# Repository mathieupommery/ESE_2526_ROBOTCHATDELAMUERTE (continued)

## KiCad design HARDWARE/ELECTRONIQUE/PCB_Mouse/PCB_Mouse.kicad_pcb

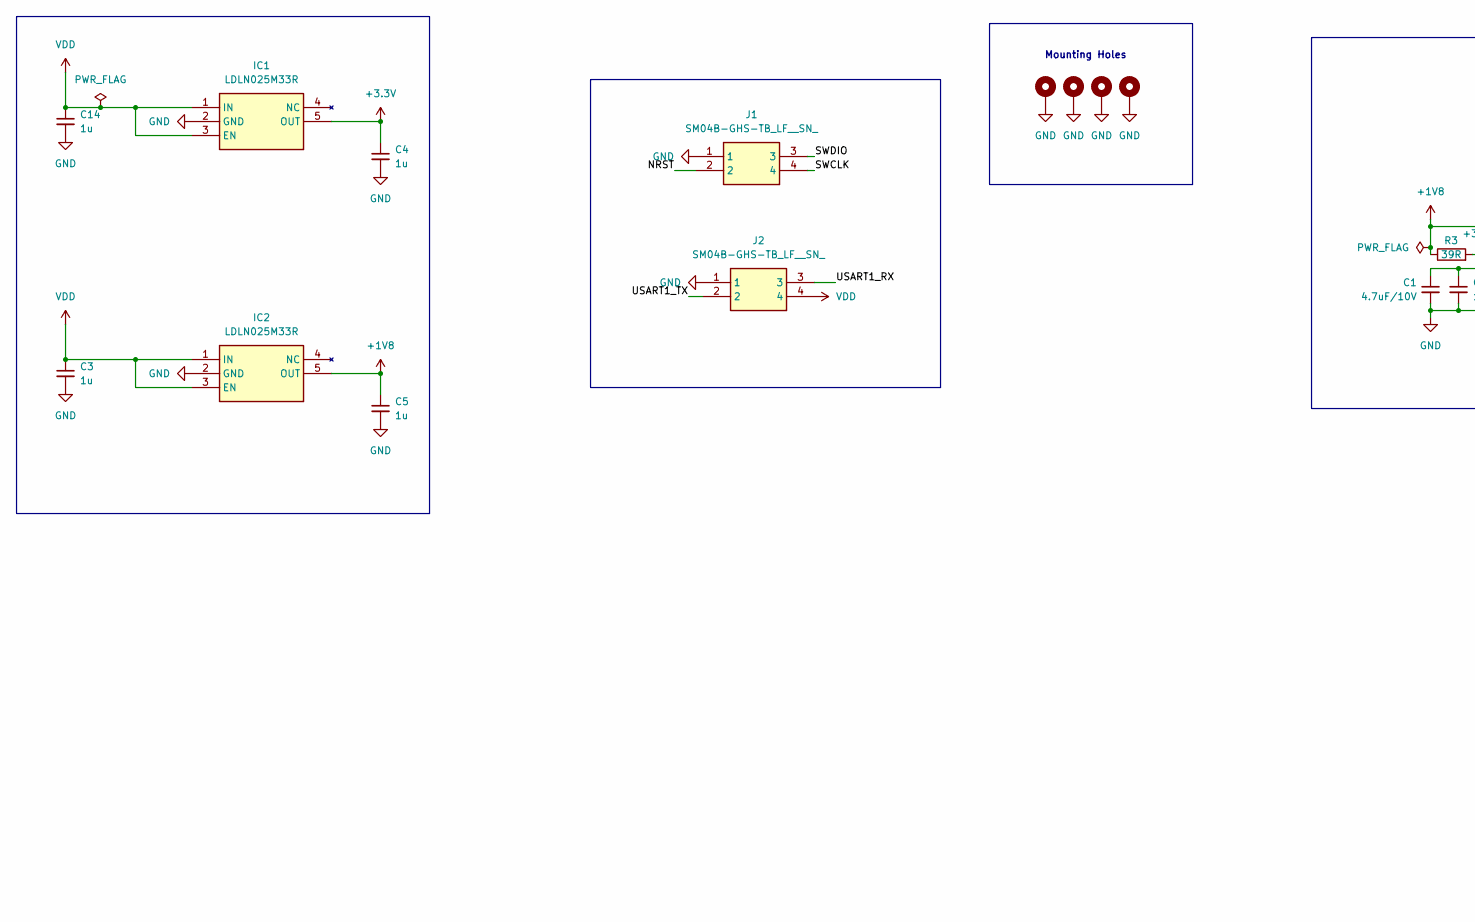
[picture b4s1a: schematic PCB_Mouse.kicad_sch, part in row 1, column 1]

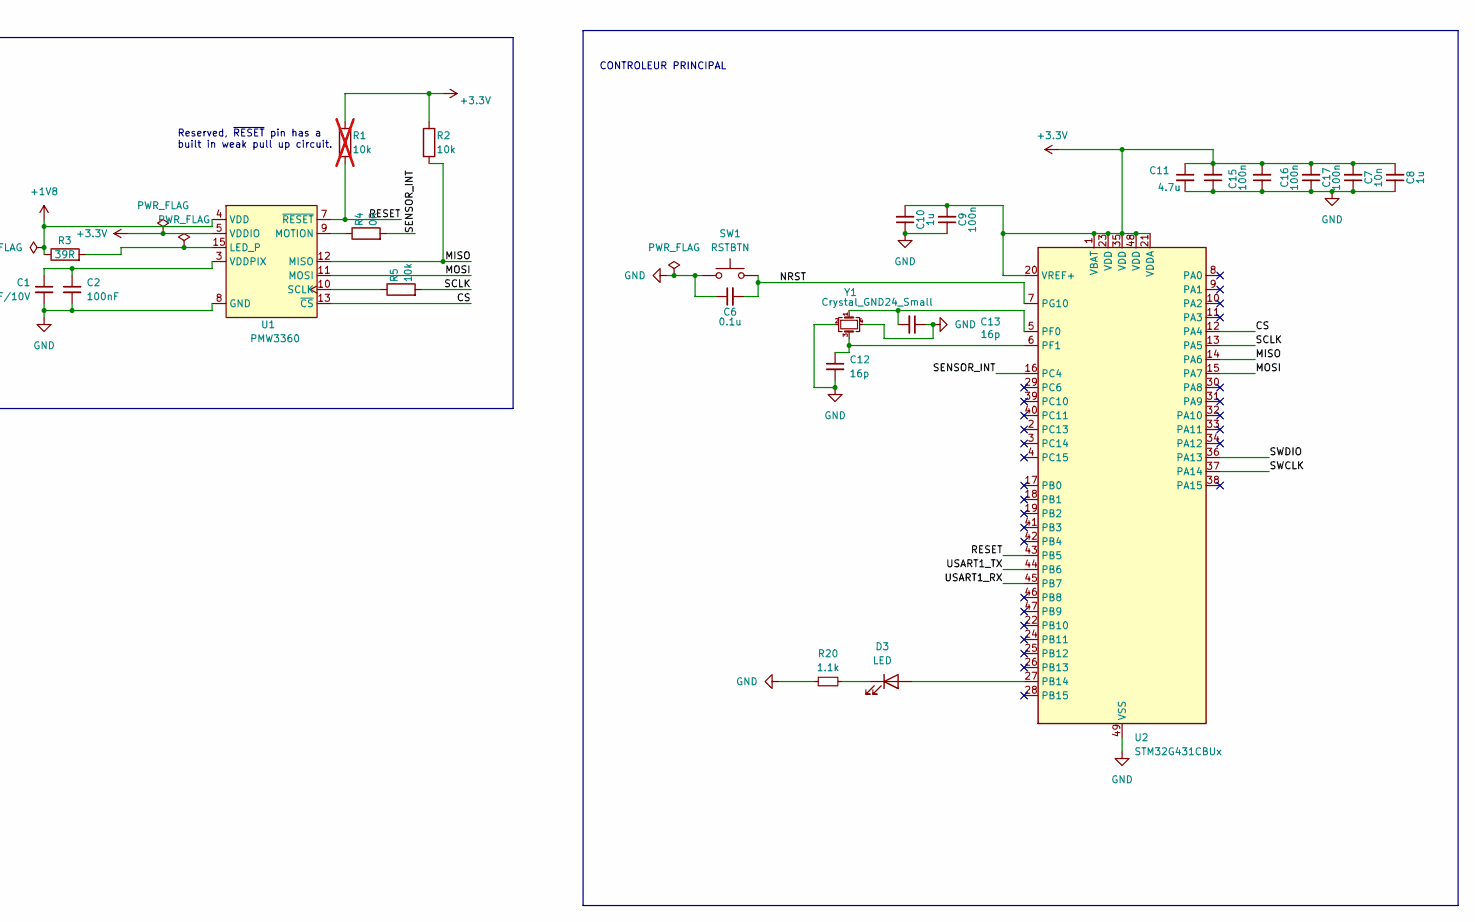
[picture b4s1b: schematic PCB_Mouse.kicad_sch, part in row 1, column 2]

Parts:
C1: 4.7uF/10V; C_0603_1608Metric_Pad1.08x0.95mm_HandSolder
C2: 100nF; C_0402_1005Metric
C3, C4, C5, C8, C10, C14: 1u; C_0402_1005Metric
C6: 0.1u; C_0402_1005Metric
C7: 10n; C_0402_1005Metric
C9, C15, C16, C17: 100n; C_0402_1005Metric
C11: 4.7u; C_0402_1005Metric
C12, C13: 16p; C_0402_1005Metric
D3: LED; LED_0402_1005Metric
H1, H2, H3, H4: MountingHole_Pad; MountingHole_2.2mm_M2_ISO14580_Pad
IC1, IC2: LDLN025M33R; SOT95P280X145-5N; Manufacturer_Part_Number LDLN025M33R; Mouser Part Number 511-LDLN025M33R
J1, J2: SM04B-GHS-TB_LF__SN_; SM04B-GHS-TB; Manufacturer_Part_Number SM04B-GHS-TB(LF)(SN); Mouser Part Number N/A
R1: 10k; R_0402_1005Metric; not fitted
R2, R5: 10k; R_0402_1005Metric
R3: 39R; R_0402_1005Metric
R4: 0R; R_0402_1005Metric
R20: 1.1k; R_0402_1005Metric
SW1: RSTBTN; KXT341LHS
U1: PMW3360
U2: STM32G431CBUx; QFN-48-1EP_7x7mm_P0.5mm_EP5.6x5.6mm
Y1: Crystal_GND24_Small; LFXTAL069527REEL

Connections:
+1V8: C5.1, IC2.5 (OUT), R3.1, U1.4 (VDD)
+3.3V: C4.1, C7.2, C8.2, C9.2, C10.2, C11.1, C15.2, C16.2, C17.2, IC1.5 (OUT), R1.1, R2.1, U1.5 (VDDIO), U2.1 (VBAT), U2.20 (VREF+), U2.21 (VDDA), U2.23 (VDD), U2.35 (VDD), U2.48 (VDD)
/CS: U1.13 (~CS), U2.12 (PA4)
/MISO: R2.2, U1.12 (MISO), U2.14 (PA6)
/MOSI: U1.11 (MOSI), U2.15 (PA7)
/NRST: C6.2, J1.2, SW1.2, U2.7 (PG10)
/RESET: R1.2, U1.7 (~RESET), U2.43 (PB5)
/SCLK: R5.2, U2.13 (PA5)
/SENSOR_INT: R4.2, U2.16 (PC4)
/SWCLK: J1.4, U2.37 (PA14)
/SWDIO: J1.3, U2.36 (PA13)
/USART1_RX: J2.3, U2.45 (PB7)
/USART1_TX: J2.2, U2.44 (PB6)
GND: C1.2, C2.2, C3.2, C4.2, C5.2, C6.1, C7.1, C8.1, C9.1, C10.1, C11.2, C12.2, C13.1, C14.2, C15.1, C16.1, C17.1, H1.1, H2.1, H3.1, H4.1, IC1.2 (GND), IC2.2 (GND), J1.1, J2.1, R20.1, SW1.1, U1.8 (GND), U2.49 (VSS), Y1.2, Y1.4
unnamed: D3.2 (A), U2.27 (PB14)
unnamed: D3.1 (K), R20.2
unnamed: R3.2, U1.15 (LED_P)
unnamed: R4.1, U1.9 (MOTION)
unnamed: R5.1, U1.10 (SCLK)
unnamed: C1.1, C2.1, U1.3 (VDDPIX)
unnamed: C13.2, U2.5 (PF0), Y1.1
unnamed: C12.1, U2.6 (PF1), Y1.3
VDD: C3.1, C14.1, IC1.1 (IN), IC1.3 (EN), IC2.1 (IN), IC2.3 (EN), J2.4

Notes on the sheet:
Reserved, ~{RESET} pin has a built in weak pull up circuit.
CONTROLEUR PRINCIPAL
Mounting Holes

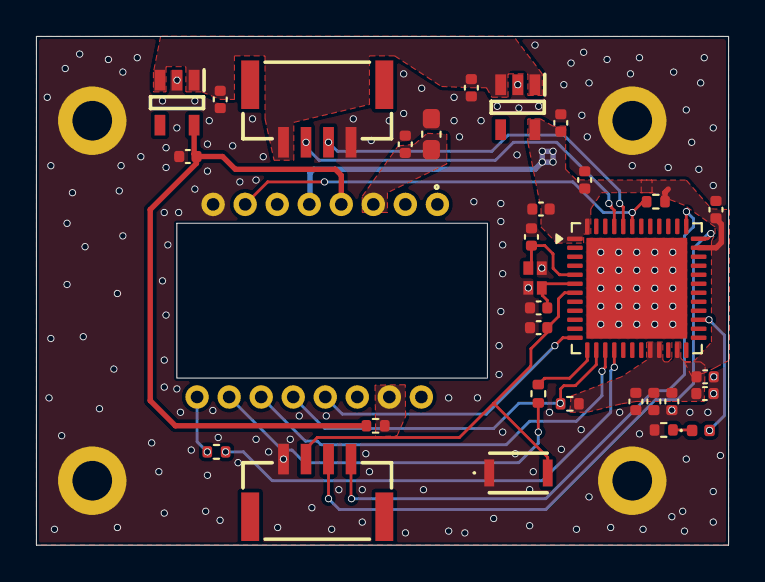
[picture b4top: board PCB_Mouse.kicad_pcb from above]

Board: 2 copper layers, 38.4 x 28.3 mm, 36 parts (0 on the bottom side), 23 nets.

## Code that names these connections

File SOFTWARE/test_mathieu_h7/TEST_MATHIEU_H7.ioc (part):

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Mcu.Name=STM32H743V(G-I)Hx
Mcu.Package=TFBGA100
Mcu.UserName=STM32H743VIHx
PA0.Mode=Asynchronous
PA0.Signal=UART4_TX
PA1.Mode=Asynchronous
PA1.Signal=UART4_RX
PA10.GPIOParameters=GPIO_Label
PA10.GPIO_Label=GPIO_MOT3
PA10.Signal=GPXTI10
PA11.Mode=Device_Only
PA11.Signal=USB_OTG_FS_DM
PA12.Mode=Device_Only
PA12.Signal=USB_OTG_FS_DP
PA13\ (JTMS/SWDIO).Mode=Serial_Wire
PA13\ (JTMS/SWDIO).Signal=DEBUG_JTMS-SWDIO
PA14\ (JTCK/SWCLK).Mode=Serial_Wire
PA14\ (JTCK/SWCLK).Signal=DEBUG_JTCK-SWCLK
PA15\ (JTDI).Signal=SPI1_NSS
PA3.Signal=GPXTI3
PA4.Signal=GPIO_Output
PA8.Mode=I2C
PA8.Signal=I2C3_SCL
PB1.Signal=S_TIM3_CH4
PB10.Mode=I2C
PB10.Signal=I2C2_SCL
PB11.Mode=I2C
PB11.Signal=I2C2_SDA
PB12.Signal=GPXTI12
PB14.Mode=Asynchronous
PB14.Signal=USART1_TX
PB15.Mode=Asynchronous
PB15.Signal=USART1_RX
PB3\ (JTDO/TRACESWO).Mode=Full_Duplex_Master
PB3\ (JTDO/TRACESWO).Signal=SPI1_SCK
PB4\ (NJTRST).Mode=Full_Duplex_Master
PB4\ (NJTRST).Signal=SPI1_MISO
PB5.Mode=Full_Duplex_Master
PB5.Signal=SPI1_MOSI
PB7.Signal=S_TIM4_CH2
PB8.Mode=I2C
PB8.Signal=I2C1_SCL
PB9.Mode=I2C
PB9.Signal=I2C1_SDA
PC0.Signal=GPXTI0
PC1.Signal=GPIO_Output
PC11.Signal=GPXTI11
PC2_C.Signal=GPXTI2
PC6.Mode=Asynchronous
PC6.Signal=USART6_TX
PC7.Mode=Asynchronous
PC7.Signal=USART6_RX
PC9.Mode=I2C
PC9.Signal=I2C3_SDA
PD0.Mode=SAI_A_Master
PD0.Signal=SAI3_SCK_A
PD1.Mode=SAI_A_Master
PD1.Signal=SAI3_SD_A
PD10.GPIOParameters=GPIO_Label
PD10.GPIO_Label=LED1
PD10.Signal=GPIO_Output
PD11.GPIOParameters=GPIO_Label
PD11.GPIO_Label=LED0
PD11.Signal=GPIO_Output
PD12.Mode=I2C
PD12.Signal=I2C4_SCL
PD13.Mode=I2C
PD13.Signal=I2C4_SDA
PD4.Mode=SAI_A_Master
PD4.Signal=SAI3_FS_A
PD8.Mode=Asynchronous
PD8.Signal=USART3_TX
PD9.Mode=Asynchronous
PD9.Signal=USART3_RX
PE0.Mode=Asynchronous
PE0.Signal=UART8_RX
PE1.Mode=Asynchronous
PE1.Signal=UART8_TX
PE15.Signal=GPIO_Output
PE2.Mode=Full_Duplex_Master
PE2.Signal=SPI4_SCK
PE5.Mode=Full_Duplex_Master
PE5.Signal=SPI4_MISO
PE6.Mode=Full_Duplex_Master
PE6.Signal=SPI4_MOSI
PE7.Mode=Asynchronous
PE7.Signal=UART7_RX
PE8.Mode=Asynchronous
PE8.Signal=UART7_TX
PH0-OSC_IN\ (PH0).Mode=HSE-External-Oscillator
PH0-OSC_IN\ (PH0).Signal=RCC_OSC_IN
PH1-OSC_OUT\ (PH1).Mode=HSE-External-Oscillator
PH1-OSC_OUT\ (PH1).Signal=RCC_OSC_OUT
RCC.HSE_VALUE=8000000
RCC.SYSCLKFreq_VALUE=480000000
RCC.SYSCLKSource=RCC_SYSCLKSOURCE_PLLCLK
board=custom

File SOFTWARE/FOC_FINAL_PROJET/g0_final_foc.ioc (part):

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Mcu.Name=STM32G031C(4-6-8)Tx
Mcu.Package=LQFP48
Mcu.UserName=STM32G031C8Tx
PA0.Mode=Full_Duplex_Master
PA0.Signal=SPI2_SCK
PA1.GPIOParameters=GPIO_Label
PA1.GPIO_Label=MGH
PA1.Signal=GPIO_Input
PA10.GPIOParameters=GPIO_Speed,GPIO_PuPd,GPIO_Label
PA10.GPIO_Label=HSW
PA10.GPIO_PuPd=GPIO_PULLDOWN
PA10.GPIO_Speed=GPIO_SPEED_FREQ_HIGH
PA10.Signal=S_TIM1_CH3
PA11\ [PA9].GPIOParameters=PinState,GPIO_PuPd,GPIO_Label
PA11\ [PA9].GPIO_Label=OC_SEL
PA11\ [PA9].GPIO_PuPd=GPIO_PULLDOWN
PA11\ [PA9].PinState=GPIO_PIN_SET
PA11\ [PA9].Signal=GPIO_Output
PA12\ [PA10].GPIOParameters=GPIO_Label
PA12\ [PA10].GPIO_Label=BTN
PA12\ [PA10].Signal=GPXTI12
PA13.Mode=Serial_Wire
PA13.Signal=SYS_SWDIO
PA14-BOOT0.Mode=Serial_Wire
PA14-BOOT0.Signal=SYS_SWCLK
PA15.GPIOParameters=GPIO_Label
PA15.GPIO_Label=HALL_CS
PA15.Signal=GPIO_Output
PA2.Mode=Asynchronous
PA2.Signal=LPUART1_TX
PA3.Mode=Asynchronous
PA3.Signal=LPUART1_RX
PA4.GPIOParameters=GPIO_Label
PA4.GPIO_Label=MGL
PA4.Signal=GPIO_Input
PA5.GPIOParameters=GPIO_Label
PA5.GPIO_Label=VBAT/TEMP
PA5.Mode=IN5
PA5.Signal=ADC1_IN5
PA6.GPIOParameters=GPIO_Label
PA6.GPIO_Label=ISNSV
PA6.Mode=IN6
PA6.Signal=ADC1_IN6
PA7.GPIOParameters=GPIO_Label
PA7.GPIO_Label=ISNSU
PA7.Mode=IN7
PA7.Signal=ADC1_IN7
PA8.GPIOParameters=GPIO_Speed,GPIO_PuPd,GPIO_Label
PA8.GPIO_Label=HSU
PA8.GPIO_PuPd=GPIO_PULLDOWN
PA8.GPIO_Speed=GPIO_SPEED_FREQ_HIGH
PA8.Signal=S_TIM1_CH1
PA9.GPIOParameters=GPIO_Speed,GPIO_PuPd,GPIO_Label
PA9.GPIO_Label=HSV
PA9.GPIO_PuPd=GPIO_PULLDOWN
PA9.GPIO_Speed=GPIO_SPEED_FREQ_HIGH
PA9.Signal=S_TIM1_CH2
PB1.GPIOParameters=GPIO_Label
PB1.GPIO_Label=ISNSW
PB1.Mode=IN9
PB1.Signal=ADC1_IN9
PB12.GPIOParameters=GPIO_PuPd,GPIO_Label
PB12.GPIO_Label=OVERCURRENT
PB12.GPIO_PuPd=GPIO_PULLDOWN
PB12.Mode=Activate-Break-Input
PB12.Signal=TIM1_BK
PB13.GPIOParameters=GPIO_Speed,GPIO_PuPd,GPIO_Label
PB13.GPIO_Label=LSU
PB13.GPIO_PuPd=GPIO_PULLDOWN
PB13.GPIO_Speed=GPIO_SPEED_FREQ_HIGH
PB13.Mode=PWM Generation1 CH1 CH1N
PB13.Signal=TIM1_CH1N
PB14.GPIOParameters=GPIO_Speed,GPIO_PuPd,GPIO_Label
PB14.GPIO_Label=LSV
PB14.GPIO_PuPd=GPIO_PULLDOWN
PB14.GPIO_Speed=GPIO_SPEED_FREQ_HIGH
PB14.Mode=PWM Generation2 CH2 CH2N
PB14.Signal=TIM1_CH2N
PB15.GPIOParameters=GPIO_Speed,GPIO_PuPd,GPIO_Label
PB15.GPIO_Label=LSW
PB15.GPIO_PuPd=GPIO_PULLDOWN
PB15.GPIO_Speed=GPIO_SPEED_FREQ_HIGH
PB15.Mode=PWM Generation3 CH3 CH3N
PB15.Signal=TIM1_CH3N
PB6.Mode=Full_Duplex_Master
PB6.Signal=SPI2_MISO
PB7.Mode=Full_Duplex_Master
PB7.Signal=SPI2_MOSI
PF0-OSC_IN\ (PF0).GPIOParameters=GPIO_Label
PF0-OSC_IN\ (PF0).GPIO_Label=LED
PF0-OSC_IN\ (PF0).Signal=GPIO_Output
RCC.HSE_VALUE=8000000
RCC.SYSCLKFreq_VALUE=64000000
RCC.SYSCLKSource=RCC_SYSCLKSOURCE_PLLCLK
board=custom

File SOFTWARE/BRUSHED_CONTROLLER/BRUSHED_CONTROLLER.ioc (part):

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Mcu.Name=STM32G431C(6-8-B)Ux
Mcu.Package=UFQFPN48
Mcu.UserName=STM32G431CBUx
PA0.Signal=S_TIM2_CH1
PA1.Signal=S_TIM2_CH2
PA11.Signal=S_TIM4_CH1
PA12.Signal=S_TIM4_CH2
PA13.Mode=Serial_Wire
PA13.Signal=SYS_JTMS-SWDIO
PA14.Mode=Serial_Wire
PA14.Signal=SYS_JTCK-SWCLK
PA4.Signal=S_TIM3_CH2
PA8.Signal=S_TIM1_CH1
PA9.Signal=S_TIM1_CH2
PB0.Signal=S_TIM3_CH3
PB1.Signal=S_TIM3_CH4
PB10.Mode=Asynchronous
PB10.Signal=USART3_TX
PB11.Mode=Asynchronous
PB11.Signal=USART3_RX
PB15.Mode=IN15-Single-Ended
PB15.Signal=ADC2_IN15
PB2.Signal=GPXTI2
PB6.Signal=S_TIM8_CH1
PB8-BOOT0.Signal=S_TIM8_CH2
PC10.Signal=GPXTI10
PC13.GPIOParameters=GPIO_Label
PC13.GPIO_Label=LED
PC13.Signal=GPIO_Output
PC4.Signal=ADC2_IN5
PC6.Signal=S_TIM3_CH1
PF0-OSC_IN.Mode=HSE-External-Oscillator
PF0-OSC_IN.Signal=RCC_OSC_IN
PF1-OSC_OUT.Mode=HSE-External-Oscillator
PF1-OSC_OUT.Signal=RCC_OSC_OUT
RCC.HSE_VALUE=24000000
RCC.SYSCLKFreq_VALUE=120000000
RCC.SYSCLKSource=RCC_SYSCLKSOURCE_PLLCLK
board=custom

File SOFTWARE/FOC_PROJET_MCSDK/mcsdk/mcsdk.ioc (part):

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Mcu.Name=STM32G031C(4-6-8)Tx
Mcu.Package=LQFP48
Mcu.UserName=STM32G031C8Tx
PA10.GPIOParameters=GPIO_Speed,GPIO_PuPd,GPIO_Label
PA10.GPIO_Label=M1_PWM_WH
PA10.GPIO_PuPd=GPIO_PULLDOWN
PA10.GPIO_Speed=GPIO_SPEED_FREQ_HIGH
PA10.Signal=S_TIM1_CH3
PA11\ [PA9].GPIOParameters=PinState,GPIO_PuPd,GPIO_Label
PA11\ [PA9].GPIO_Label=OC_SEL
PA11\ [PA9].GPIO_PuPd=GPIO_PULLDOWN
PA11\ [PA9].PinState=GPIO_PIN_SET
PA11\ [PA9].Signal=GPIO_Output
PA13.GPIOParameters=GPIO_Label
PA13.GPIO_Label=TMS
PA13.Mode=Serial_Wire
PA13.Signal=SYS_SWDIO
PA14-BOOT0.GPIOParameters=GPIO_Label
PA14-BOOT0.GPIO_Label=TCK
PA14-BOOT0.Mode=Serial_Wire
PA14-BOOT0.Signal=SYS_SWCLK
PA4.GPIOParameters=GPIO_Label
PA4.GPIO_Label=M1_BUS_VOLTAGE
PA4.Mode=IN4
PA4.Signal=ADC1_IN4
PA5.GPIOParameters=GPIO_Label
PA5.GPIO_Label=M1_TEMPERATURE
PA5.Mode=IN5
PA5.Signal=ADC1_IN5
PA6.GPIOParameters=GPIO_Label
PA6.GPIO_Label=M1_CURR_AMPL_U
PA6.Mode=IN6
PA6.Signal=ADC1_IN6
PA7.GPIOParameters=GPIO_Label
PA7.GPIO_Label=M1_CURR_AMPL_V
PA7.Mode=IN7
PA7.Signal=ADC1_IN7
PA8.GPIOParameters=GPIO_Speed,GPIO_PuPd,GPIO_Label
PA8.GPIO_Label=M1_PWM_UH
PA8.GPIO_PuPd=GPIO_PULLDOWN
PA8.GPIO_Speed=GPIO_SPEED_FREQ_HIGH
PA8.Signal=S_TIM1_CH1
PA9.GPIOParameters=GPIO_Speed,GPIO_PuPd,GPIO_Label
PA9.GPIO_Label=M1_PWM_VH
PA9.GPIO_PuPd=GPIO_PULLDOWN
PA9.GPIO_Speed=GPIO_SPEED_FREQ_HIGH
PA9.Signal=S_TIM1_CH2
PB1.GPIOParameters=GPIO_Label
PB1.GPIO_Label=M1_CURR_AMPL_W
PB1.Mode=IN9
PB1.Signal=ADC1_IN9
PB12.GPIOParameters=GPIO_PuPd,GPIO_Label
PB12.GPIO_Label=M1_OCP
PB12.GPIO_PuPd=GPIO_PULLDOWN
PB12.Mode=Activate-Break-Input
PB12.Signal=TIM1_BK
PB13.GPIOParameters=GPIO_Speed,GPIO_PuPd,GPIO_Label
PB13.GPIO_Label=M1_PWM_UL
PB13.GPIO_PuPd=GPIO_PULLDOWN
PB13.GPIO_Speed=GPIO_SPEED_FREQ_HIGH
PB13.Mode=PWM Generation1 CH1 CH1N
PB13.Signal=TIM1_CH1N
PB14.GPIOParameters=GPIO_Speed,GPIO_PuPd,GPIO_Label
PB14.GPIO_Label=M1_PWM_VL
PB14.GPIO_PuPd=GPIO_PULLDOWN
PB14.GPIO_Speed=GPIO_SPEED_FREQ_HIGH
PB14.Mode=PWM Generation2 CH2 CH2N
PB14.Signal=TIM1_CH2N
PB15.GPIOParameters=GPIO_Speed,GPIO_PuPd,GPIO_Label
PB15.GPIO_Label=M1_PWM_WL
PB15.GPIO_PuPd=GPIO_PULLDOWN
PB15.GPIO_Speed=GPIO_SPEED_FREQ_HIGH
PB15.Mode=PWM Generation3 CH3 CH3N
PB15.Signal=TIM1_CH3N
PB6.GPIOParameters=GPIO_Speed,GPIO_PuPd,GPIO_Label,GPIO_Mode
PB6.GPIO_Label=UART_TX
PB6.GPIO_Mode=GPIO_MODE_AF_PP
PB6.GPIO_PuPd=GPIO_NOPULL
PB6.GPIO_Speed=GPIO_SPEED_FREQ_LOW
PB6.Mode=Asynchronous
PB6.Signal=USART1_TX
PB7.GPIOParameters=GPIO_Speed,GPIO_PuPd,GPIO_Label,GPIO_Mode
PB7.GPIO_Label=UART_RX
PB7.GPIO_Mode=GPIO_MODE_AF_PP
PB7.GPIO_PuPd=GPIO_NOPULL
PB7.GPIO_Speed=GPIO_SPEED_FREQ_LOW
PB7.Mode=Asynchronous
PB7.Signal=USART1_RX
PC14-OSC32_IN\ (PC14).GPIOParameters=GPIO_PuPd,GPIO_Label,GPIO_ModeDefaultEXTI
PC14-OSC32_IN\ (PC14).GPIO_Label=Start/Stop [PushButton]
PC14-OSC32_IN\ (PC14).GPIO_ModeDefaultEXTI=GPIO_MODE_IT_FALLING
PC14-OSC32_IN\ (PC14).GPIO_PuPd=GPIO_PULLUP
PC14-OSC32_IN\ (PC14).Signal=GPXTI14
RCC.HSE_VALUE=8000000
RCC.SYSCLKFreq_VALUE=64000000
RCC.SYSCLKSource=RCC_SYSCLKSOURCE_PLLCLK
board=custom

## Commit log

2025-09-09 DXF model of 2804 BL
2025-09-09 DXF + mecanique
2025-09-11 update foc
2025-09-12 lidar test nucleo
2025-09-12 jgfffn
2025-09-19 LiDAR + PAPI
2025-09-19 update pcb papi
2025-09-22 PCB Principal
2025-09-23 updfate
2025-09-26 up pcb principal
2025-10-02 push
2025-10-03 up hall
2025-10-11 testlorenzoh7
2025-10-13 mouse
2025-10-17 TOF sur le paf
2025-10-19 pcb v2
2025-10-21 Update README with V2 specifications
    Added details for V2 of the motherboard and FOC STM32 based controller.
2025-10-21 Add images for V2 in README
    Added images for V2 of the project in the README.
2025-10-21 Revise README for V2 hardware specifications
    Updated README to reflect changes in hardware specifications and features for V2, including audio processing improvements and new components.
2025-10-21 Enhance README with V2 audio and hardware details
    Updated README to include improvements in audio processing and hardware changes.
2025-10-21 Photos Robot PAF
2025-10-21 Added CAD images
2025-10-30 up brushed
2025-11-25 TOF test
2025-11-28 lidar fonctionne bien
2025-11-30 failsafe push
2025-12-03 ni**a
2025-12-03 cluster detction sorta working
2025-12-04 CLusterization readable and efficient
    TODO Hole filling
2025-12-05 cluster hole handling
2025-12-05 added to final firmware
2025-12-05 memcpy working
2025-12-11 SOFTWARE LORENZO BRNACH
2025-12-21 JBDVSJSBV
2026-01-08 Revise README for clarity and organization
    Updated the README to enhance project details, including introduction, hardware, and software sections. Improved clarity and organization with a new table of contents.
2026-01-09 added drifting?
2026-01-21 Fix typo in features section of README
    Corrected 'ia' to 'AI' in features description for clarity.
2026-01-23 Fix formatting in README.md for strategy implementation
2026-01-23 Fix typos in README.md section titles
2026-01-23 Fix typo in 'Strategy Implementation' section
2026-01-23 Renumber Strategy Implementation section in README
    Updated section numbering in README.md from 4 to 5.
2026-01-24 pimp update
